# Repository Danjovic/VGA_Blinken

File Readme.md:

# VGA Blinking Lights
This project consists of a a device capable of generating a (pseudo) random blinking lights pattern. The objective of this project is to turn old monitors, specially CRTs, into decorative objects.

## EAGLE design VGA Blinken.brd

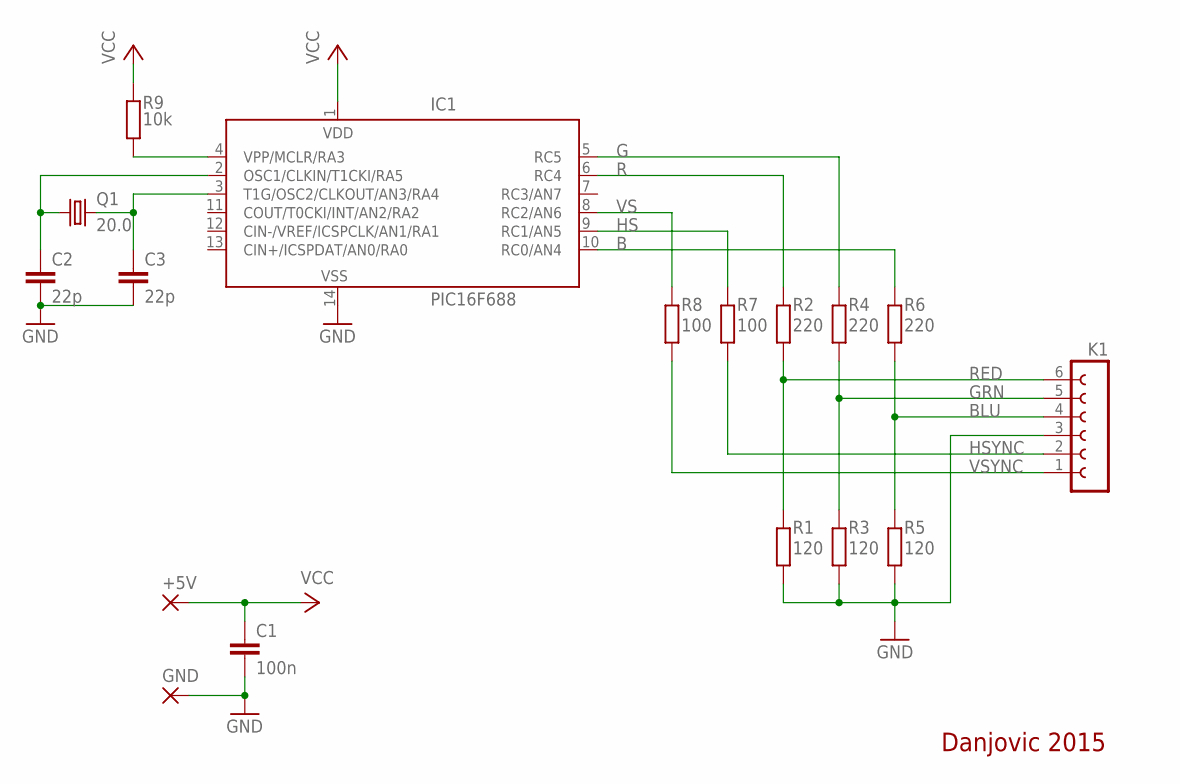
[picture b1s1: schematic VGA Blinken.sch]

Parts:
+5V: 1,6/0,8
C1: 100n; C025-024X044L
C2, C3: 22p; C025-024X044L
GND: 1,6/0,8
IC1: PIC16F688; DIL14
K1: FE06-1; FE06
Q1: 20.0; HC49/S
R1, R3, R5: 120; 0204VL
R2, R4, R6: 220; 0204VL
R7, R8: 100; 0204VL
R9: 10k; 0204VL

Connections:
B: IC1.10 (RC0/AN4), R6.2
BLU: K1.4, R5.1, R6.1
G: IC1.5 (RC5), R4.2
GND: C1.2, C2.2, C3.2, GND.1, IC1.14 (VSS), K1.3, R1.2, R3.2, R5.2
GRN: K1.5, R3.1, R4.1
HS: IC1.9 (RC1/AN5), R7.2
HSYNC: K1.2, R7.1
R: IC1.6 (RC4), R2.2
RED: K1.6, R1.1, R2.1
RST: IC1.4 (VPP/MCLR/RA3), R9.2
VCC: +5V.1, C1.1, IC1.1 (VDD), R9.1
VS: IC1.8 (RC2/AN6), R8.2
VSYNC: K1.1, R8.1
X1: C2.1, IC1.2 (OSC1/CLKIN/T1CKI/RA5), Q1.1
X2: C3.1, IC1.3 (T1G/OSC2/CLKOUT/AN3/RA4), Q1.2

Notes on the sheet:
Danjovic 2015

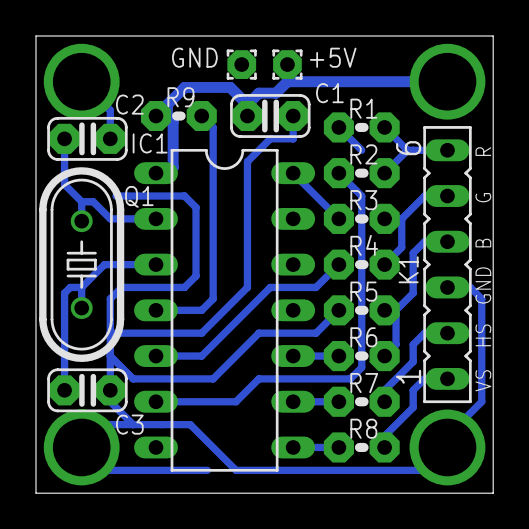
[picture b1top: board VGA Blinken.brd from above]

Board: 2 copper layers, 25.4 x 25.4 mm, 17 parts (0 on the bottom side), 15 nets.

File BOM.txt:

Partlist exported from C:/Users/user/Documents/GitHub/VGA_Blinken/circuit/VGA Blinken.sch at 28/11/2015 11:41:27

Part Value     Device        Package       Description                                    MF        MPN           OC_FARNELL OC_NEWARK
+5V            1,6/0,8       1,6/0,8       THROUGH-HOLE PAD                                                                           
C1   100n      C-EU          C025-024X044L CAPACITOR, European symbol                                                                 
C2   22p       C-EU          C025-024X044L CAPACITOR, European symbol                                                                 
C3   22p       C-EU          C025-024X044L CAPACITOR, European symbol                                                                 
GND            1,6/0,8       1,6/0,8       THROUGH-HOLE PAD                                                                           
IC1  PIC16F688 PIC16F676P    DIL14         14-Pin, Flash-Based 8-Bit CMOS Microcontroller MICROCHIP PIC16F676-I/P 9760512    54K2829  
K1             FE06-1        FE06          FEMALE HEADER                                                          unknown    unknown  
Q1   20.0      CRYSTALHC49S  HC49/S        CRYSTAL                                                                1667008    unknown  
R1   120       R-EU_0204/2VL 0204VL        RESISTOR, European symbol                                                                  
R2   220       R-EU_0204/2VL 0204VL        RESISTOR, European symbol                                                                  
R3   120       R-EU_0204/2VL 0204VL        RESISTOR, European symbol                                                                  
R4   220       R-EU_0204/2VL 0204VL        RESISTOR, European symbol                                                                  
R5   120       R-EU_0204/2VL 0204VL        RESISTOR, European symbol                                                                  
R6   220       R-EU_0204/2VL 0204VL        RESISTOR, European symbol                                                                  
R7   100       R-EU_0204/2VL 0204VL        RESISTOR, European symbol                                                                  
R8   100       R-EU_0204/2VL 0204VL        RESISTOR, European symbol                                                                  
R9   10k       R-EU_0204/2VL 0204VL        RESISTOR, European symbol

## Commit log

2015-11-25 :octocat: Added .gitattributes & .gitignore files
2015-11-25 Basic Release
    Basic release. The firmware can generate a VGA color bar pattern. This
    is the baseline for the rest of the project.
2015-11-25 PCB files moved to its own folder
2015-11-28 First working version
2015-11-28 Just a Readme
2015-11-28 Added License files
2015-11-28 Excluded CAM files from gitignore
2015-11-28 Added Gerber Files
